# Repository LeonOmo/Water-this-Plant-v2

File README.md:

# Water this Plant v2

This is an upgrade the v1 of WtP - a simple project to monitor soil moisture lvls for my plant, featuring LED feedback and phone alerts when watering is needed. Uses small solar panels for recharging the batteries and a sleep mode for less energie usage

## Why does it exist?

- Responsibility: I have a plant of my own, and instead of watering it randomly, I want to water it only when it really needs water. That way I can take better care of it.
- Sensors: I've been building projects with many different sensors so that I can work with any kind of sensor.
- Phone messages: This is the first project where I can get messages on my phone

## Features

- Visual Alerts: 2x LEDs notifying me when the plant needs water (Red = need moisture, Green / Blue = enough moisture).
- Phone Alert: Notifies my phone when the plant needs water.
- Solar Power System: Setup using a 5V solar panels and a battery, protected by a diode for continuous usage without manual recharging (or constant connection).

## Components 

- Microcontroller: Wemos Lolin D32 
- Sensor: Capacitive Soil Moisture Sensor v1.2
- Power & Solar: 
  - 1x Rechargeable battery
  - 1x 5V / 0.3W Mini Solar Panels (68x36 mm)
  - 1x Diode (reverse current protection)
- LEDs: 1x Green / Blue LED & 1x Red LED
- Resistors: 2x 220 Ohm Resistors
- Connecting everything: PCB

## Tools

- Paint: Used for making the idea
- TinkerCAD: Reference made here
- Onshape: Designed the CAD there
- Arduino IDE: Firmware
- KiCAD: PCB Design

## Schematic

## PCB

## Firmware

## CAD

- Case Design
https://cad.onshape.com/documents/1d40b63780d7c86f761a8abb/w/1eb81e265bd99f0ddb002a3f/e/59044aae10a250925d74491d?renderMode=0&uiState=6ada7ccf6d0bc2ecbc7e4ee0

## Extras

- Credits: My friend gave me the idea. Fun project with first time using wifi and the moisture sensor.
- OmoCat: Silkscreen on the PCB (Only on my PCB not in the files)

## Bonus

The Build Guide

- The Idea Sketch

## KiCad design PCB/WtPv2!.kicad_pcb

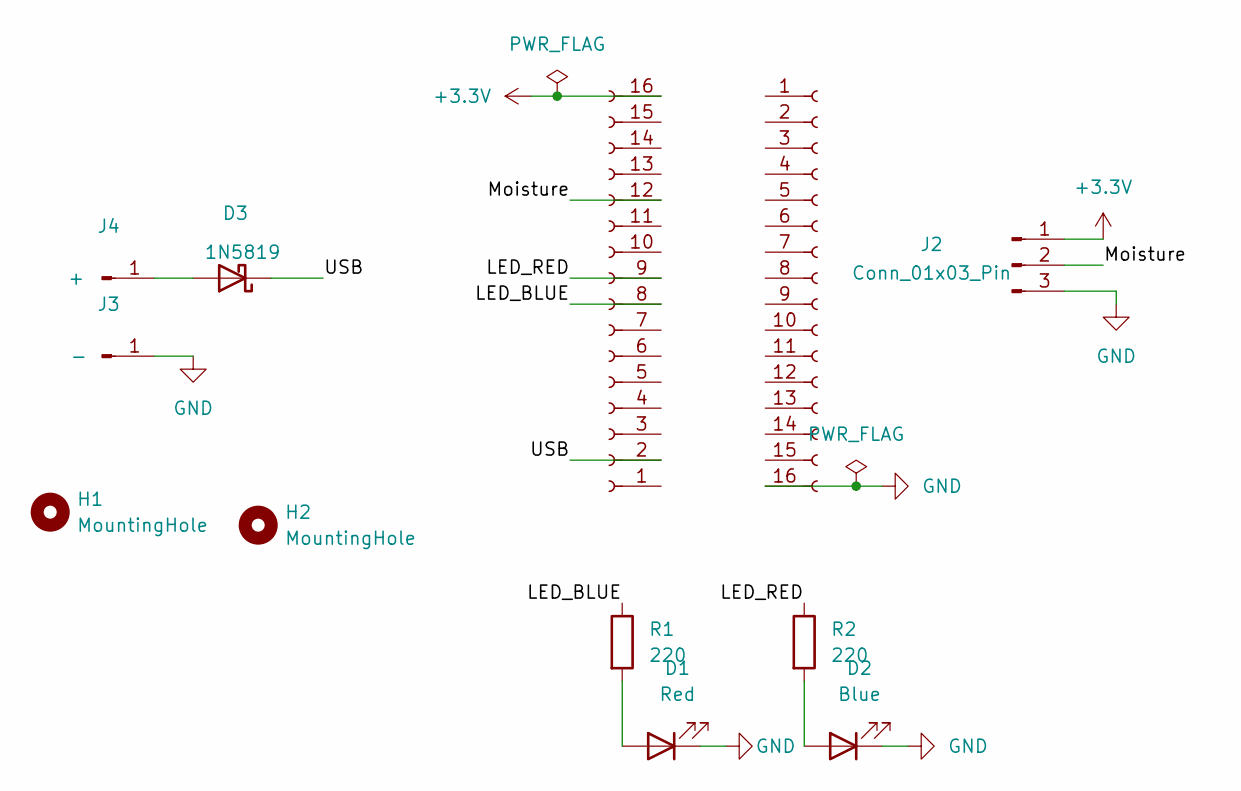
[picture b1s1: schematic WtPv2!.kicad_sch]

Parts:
-1: Conn_01x16_Socket; PinSocket_1x16_P2.54mm_Vertical
D1: Red; LED_D5.0mm
D2: Blue; LED_D5.0mm
D3: 1N5819; D_DO-41_SOD81_P10.16mm_Horizontal
H1, H2: MountingHole; MountingHole_3mm
J1: Conn_01x16_Socket; PinSocket_1x16_P2.54mm_Vertical
J2: Conn_01x03_Pin; PinHeader_1x03_P2.54mm_Horizontal
J3: -; TestPoint_Pad_4.0x4.0mm
J4: +; TestPoint_Pad_4.0x4.0mm
R1, R2: 220; R_Axial_DIN0204_L3.6mm_D1.6mm_P7.62mm_Horizontal

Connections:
+3.3V: J1.16, J2.1
/LED_BLUE: J1.8, R1.1
/LED_RED: J1.9, R2.1
/Moisture: J1.12, J2.2
/USB: D3.1 (K), J1.2
GND: -1.16 (Pin_16_16), D1.1 (K), D2.1 (K), J2.3, J3.1 (Pin_1_1)
unnamed: D1.2 (A), R1.2
unnamed: D2.2 (A), R2.2
unnamed: D3.2 (A), J4.1 (Pin_1_1)

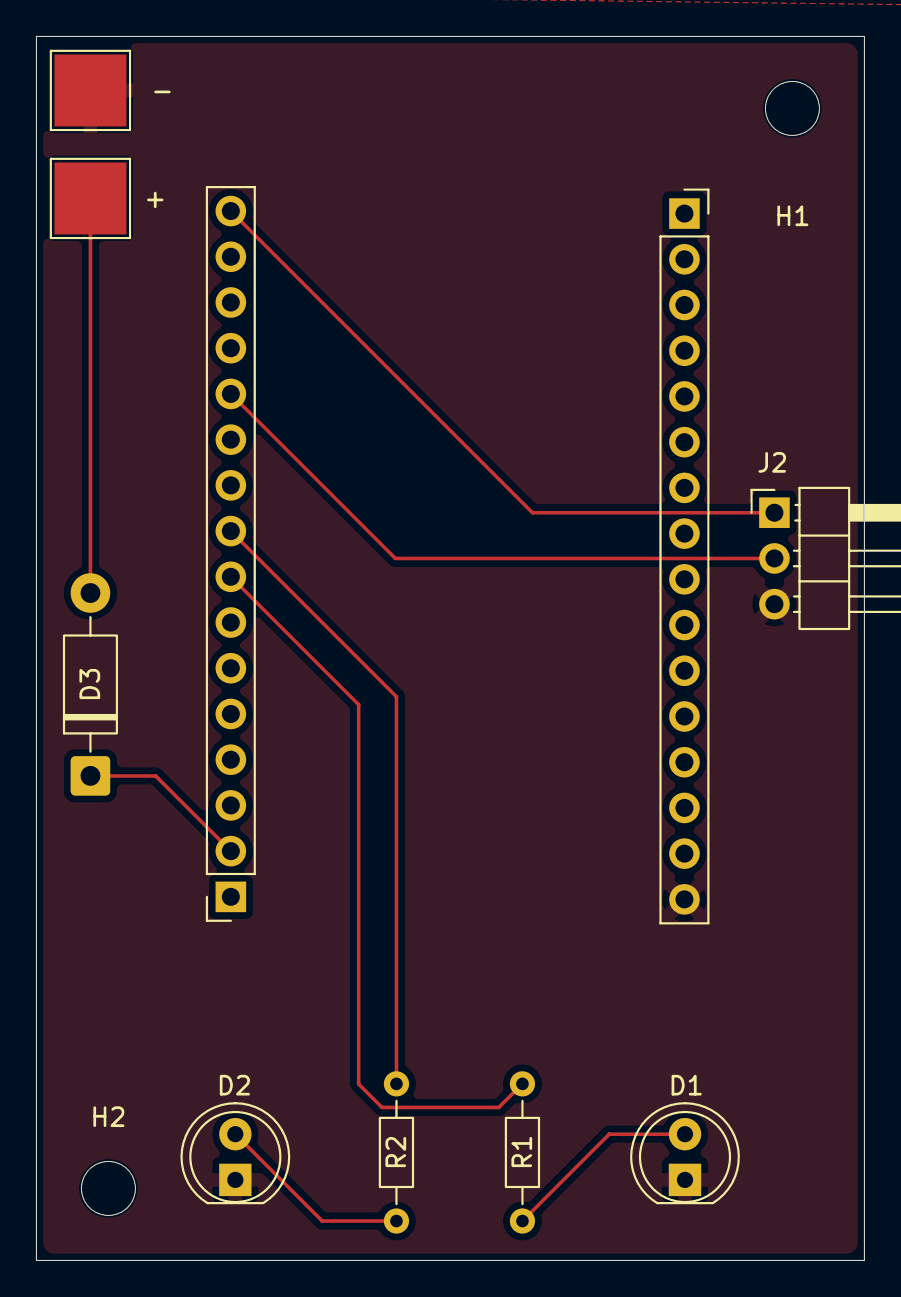
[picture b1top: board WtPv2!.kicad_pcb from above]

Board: 2 copper layers, 46.0 x 68.0 mm, 12 parts (0 on the bottom side), 9 nets.

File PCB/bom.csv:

Designator,Footprint,Quantity,Value,LCSC Part #
"-1, J1",PinSocket_1x16_P2.54mm_Vertical,2,Conn_01x16_Socket,
D1,LED_D5.0mm,1,Red,
D2,LED_D5.0mm,1,Blue,
D3,D_DO-41_SOD81_P10.16mm_Horizontal,1,1N5819,
J2,PinHeader_1x03_P2.54mm_Horizontal,1,Conn_01x03_Pin,
J3,TestPoint_Pad_4.0x4.0mm,1,-,
J4,TestPoint_Pad_4.0x4.0mm,1,+,
"R1, R2",R_Axial_DIN0204_L3.6mm_D1.6mm_P7.62mm_Horizontal,2,220,
